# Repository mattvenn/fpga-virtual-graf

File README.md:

# FPGA Virtual Graffiti

[videos and construction photos](https://photos.app.goo.gl/kivlfcmlp4oecVpu1)

# Tools used

* [icestorm](http://www.clifford.at/icestorm/) opensource FPGA tools.
* [mystorm](https://mystorm.uk/) open hardware FPGA development board
* [gtkwave](http://gtkwave.sourceforge.net/) for debugging.

# Top resource tips

* [Obijuan's FPGA tutorial](https://github.com/Obijuan/open-fpga-verilog-tutorial/wiki)
* [FPGAwars forum](https://groups.google.com/forum/#!forum/fpga-wars-explorando-el-lado-libre)
* [Dan's FPGA blog](http://www.zipcpu.com/)

# Documentation

* [system overview diagram](docs/module_overview.svg)
* Yosys can generate output graphs of the verilog with the [show](http://www.clifford.at/yosys/cmd_show.html) command.
* [schematic for mystorm](https://gitlab.com/Folknology/mystorm/blob/BlackIce/BlackIce-schematic.pdf)
* [ICEfloorplan](https://knielsen.github.io/ice40_viewer/ice40_viewer.html) can be used to show how the design is laid out on the FPGA
* [All Verilog source](src) and [tests](tests)

# Build notes

## Synthesis

    make

To program the mystorm board, first start a terminal listening on /dev/ttyUSBX
at 115200 baud, and reset the board. Then type:

    make prog

## Tests

many test benches are in [tests](tests). They can be simulated and outputs
viewed with gtkwave:

    make debug-[name of verilog file]

eg

    make debug-bresenham
    
## Storing configuration on the board

[Instructions
here](https://forum.mystorm.uk/t/config-from-non-voltatile-memory/242/2)

## SRAM video buffer

Using the SRAM on the back of the board for persistant graffitis. This caused 2
major issues:

* [PLL and SRAM pins collide on the board layout](https://forum.mystorm.uk/t/placement-conflict-between-sb-io-for-ram-and-pll/224/12)
* [switching the SB_IO pins and SRAM pins at the same time](https://forum.mystorm.uk/t/fpga-unreliability-crashing-hanging/252/19) caused instability.

## Wiimote Camera

* (breakout board)[https://github.com/mattvenn/kicad/tree/master/wiimote-fpga)
* 25mhz supplied on clock pin
* reset high to run
* wiimote camera PCB was tested with branch wii-pcb

## I2C reader / writer

Started off with this youtube series:https://www.youtube.com/watch?v=rWzB5hZlqBA
by Tom Briggs.

In Tom's design, the I2C clock is assigned to the state machine's !clk.

Writing and requesting data was easy, but reading the data was difficult to
synchronize the clock. I then tried 2 different approaches:

* separating the I2C clock and state machine clock to give more time for reading
 data (4 state machine clocks for 1 I2C clock)
* generating the clock within the state machine itself.

Option 2 proved much easier to write. I also found this [brief Q&A on reddit on
the same topic](https://m.reddit.com/r/FPGA/comments/4oltue/when_writing_communication_protocols_spi_i2c_etc/)

## DVI output

based on [Hamster's minimal DVI-D
VHDL](http://hamsterworks.co.nz/mediawiki/index.php/Minimal_DVI-D)

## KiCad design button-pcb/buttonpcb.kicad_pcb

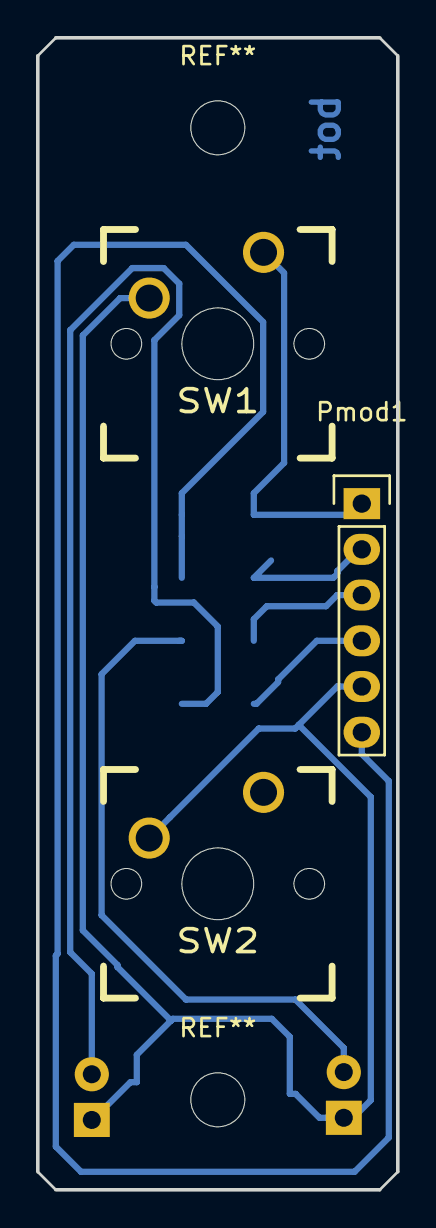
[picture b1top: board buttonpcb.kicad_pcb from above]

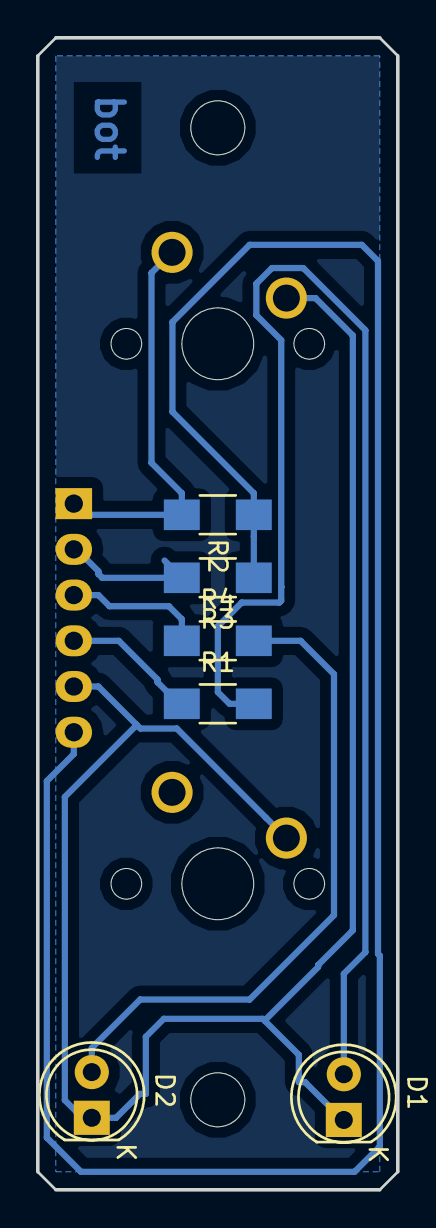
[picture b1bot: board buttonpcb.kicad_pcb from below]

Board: 2 copper layers, 20.0 x 64.0 mm, 9 parts (6 on the bottom side), 8 nets.

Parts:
D1, D2: LED; LED-5MM
Pmod1: CONN_01X06; Pin_Header_Straight_1x06
R1, R2, R3, R4: R; R_1206_HandSoldering
SW1, SW2: SW_PUSH; CHERRY_MX

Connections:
/b1: Pmod1.2, R3.2, SW2.1
/b2: Pmod1.1, R2.2, SW1.1
/led: Pmod1.4, R1.1
/led2: Pmod1.3, R4.1
Earth: D1.1, D2.1, Pmod1.5, SW1.2, SW2.2
unnamed: D1.2, R1.2
unnamed: D2.2, R4.2
VCC: Pmod1.6, R2.1, R3.1

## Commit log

2016-10-27 i2c state machine
2016-10-28 valid i2c
2016-10-28 sending single packet on button press
2016-11-01 testbenches and split things up further - works to send 2 packets
2016-11-03 button works, and faster i2c clock
2016-11-03 multi byte sending
2016-11-06 tristate sda
2016-11-06 comments
2016-11-06 rw looks like its working
2016-11-07 button pulse & test
2016-11-07 tidy
2016-11-08 moved config to new file
2016-11-24 camera i2c reads working
2016-11-24 gtkwave state files
2016-11-24 proof!
2016-11-25 leds to show where sensor detects ir led
2016-12-06 readme
2016-12-06 comments on read issue
2016-12-06 gtk write file
2016-12-06 i2c read fail docs
2016-12-07 fixed reading from i2c_sda_tri bug
2016-12-07 fixed tristate issue with 2 pins
2016-12-08 reading data again
2016-12-08 showing i2c bytes on debug byte
2016-12-24 comment
2016-12-24 comment and re-order
2016-12-24 gtkw
2016-12-26 seems to work
2016-12-26 data rx seems to be working, sums are broken
2016-12-26 maths working?
2016-12-26 combined operations
2016-12-28 fixed broken camera maths, only show leds if data is valid
2016-12-29 overview
2016-12-29 overview pic
2016-12-29 original
2017-02-27 notes
2017-02-27 flip
2017-02-27 formatting
2017-02-28 added dvi, shows a cross hair
2017-05-07 partially working with blackice board - hangs after some seconds
2017-06-10 working with wii pcb
2017-06-10 working with 25mhz clock supplied from fpga pll
2017-06-25 better demo
2017-08-16 missing sram
2017-08-28 traced pll issue and now builds but without full sram bus
2017-08-28 added missing sram
2017-09-03 output counter onto video, only increment when button is not pressed
2017-09-03 use a 640bit register to represent a line and refresh this from SRAM every new line
2017-09-03 added camera
2017-09-03 work in progress, sram video buffer working, wiimote cam not
2017-09-04 can control blocks of 16 pixels with camera
2017-09-04 working with 16 bit wide pixels
2017-09-04 draws in 16 blocks
2017-09-10 work in progress on single pixel updates
2017-09-10 reset
2017-09-10 debugging with pmod
2017-09-11 notes on problems
2017-09-11 vga test bench
2017-09-11 reset line
2017-09-11 vga reset
2017-09-11 remove tristate comment as problem is on clock not sda
2017-09-11 sram vga test bench
2017-09-11 zero data_read register on reset
2017-09-11 updated clock divider and made testbench
2017-09-11 explicit control of inout pin direction
2017-09-11 clock divider and encode state machine state onto pmod
2017-09-12 separating pix buff from top
2017-09-12 added camera write
2017-09-12 README update after merge
2017-09-12 changed to 8 bit pixel buffer
2017-09-13 single pixel drawing
2017-09-13 missing sram testbench
2017-09-13 sram simulation updated to show counter
2017-09-14 lines docs
2017-09-14 bresenham algorithm tested
2017-09-14 line calculations
2017-09-16 map camera output range to screen size
2017-09-17 line is starting to draw but lots of issues
2017-09-17 added clken to write_buffer so erase can continue
2017-09-17 fix wrap issue in pix buffer
2017-09-17 line drawing with start and stop - intermittent glitch
2017-09-18 fixed line glitch
2017-09-18 additional files
2017-09-18 image docs
2017-09-18 localparam for config
2017-09-19 added button board
2017-09-19 persistance settings
2017-09-20 clock enabled camera modules
2017-09-21 smaller data register
2017-09-21 simplified now running at 25Mhz
2017-09-21 switched to array for more efficient synthesis
2017-09-22 fat lines
2017-09-22 ignore
2017-09-22 cleanup
2017-09-22 removed button
2017-09-22 fixed trailing comma
2017-09-22 moved things around for cleaner top directory, separated tests
2017-09-22 missing gtkw file
2017-09-22 missing gtkw files
2017-09-22 ignore file
2017-09-22 renamed i2c to top, changed project name to vgraf
2017-10-07 perma program
2017-10-11 fixed camera bug by delaying start of i2c comms
2017-10-11 removed i2c debugging
2017-10-11 fixed test
2017-10-11 fix startup bug
2017-10-14 dot file example for creating graphical description of the map_cam.v module
2017-10-15 generate svg from verilog port definition
2017-10-15 rule for making svg module ports
2017-10-22 rename function
2017-10-22 clean more files
2017-10-22 overview diagram
2017-10-22 show wire or reg by closed or open box
2017-10-22 unneeded file
2017-10-22 a3 overview
2017-10-22 updated overview pic
2017-10-22 handle ps files
2017-10-22 formatting, move todo to separate file
2017-10-22 fix up module overview
2017-10-22 fix link to overview
2017-10-24 added colour to vga module
2017-10-24 pulse test bench
2017-10-25 only draw pixels from buffer when out of the border
2017-10-26 add links to useful docs
2017-10-30 better rule for module svg
2017-10-30 basename for svg
2017-10-30 ignores
2017-10-30 hard code template path
2019-01-16 mention video specifically
